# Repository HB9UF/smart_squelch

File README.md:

HB9UF Smart Squelch -- A squelch board with clever logic
========================================================

A typical FM squelch for voice operation quantifies the amount of noise at frequencies above the voice frequency content and opens if said noise energy is sufficiently low. This works because without any input RF signal present, the FM detector produces wideband noise, reaching frequencies of several dozen kHz. A sufficiently strong RF input reduces that noise, the modulation emerges between typically 0 and 3 kHz and similarly, the noise above 3 kHz is reduced. Traditionally, a high-pass filter (HPF) attenuates the modulation while retaining the noise energy, and a subsequent peak-detector quantifies the amount of energy present, and finally a comparator circuit uses the peak detector output voltage to actuate the squelch.

Our squelch circuit is different. First, we use a microcontroller for the squelch logic. This allows us not only to change squelch thresholds without hardware access, but we can also implement more sophisticated squelching logic. For example, we can implement a hard threshold that is used when strong stations key off: The squelch is closed immediately, minimizing the squelch crash that is nothing but the manifestation of discriminator noise during the time-window after key-off and the closing of the squelch. At the same time, we can implement a second threshold for weak stations, e.g. stations far away, with low RF power, fading stations, or mobile stations with picket-fencing. Such stations may overcome the weak, but not the strong threshold. In this case, the squelch remains open for a predetermined time-window (e.g. 1 second) in order not to cut off the weak station. Note that this is superior to simply adding hysteresis to the aforementioned comparator, and that this is mimicking the behaviour of the [MICOR Squelch](http://www.repeater-builder.com/micor/micor-bi-level-squelch-theory.html) system.

The board also contains a number of extra circuitry such as an anti-aliasing low pass filter, a DC/DC converter etc. for integration with our repeater controller. This project is fully open source, the hardware is released under the CC-BY-SA license and the firmware is released under the GPL 2 license. Instructions for compiling and flashing the firmware are documented in a `README` file in the `firmware` subdirectory. The necessary tools and frameworks (ChibiOS and stm32flash) are also included there as git submodules. The circuitry was developed to improve the poor squelch performance of the Yaesu DR-1X repeater and is also successfully used in a number of homebrew 1.3 GHz repeaters.

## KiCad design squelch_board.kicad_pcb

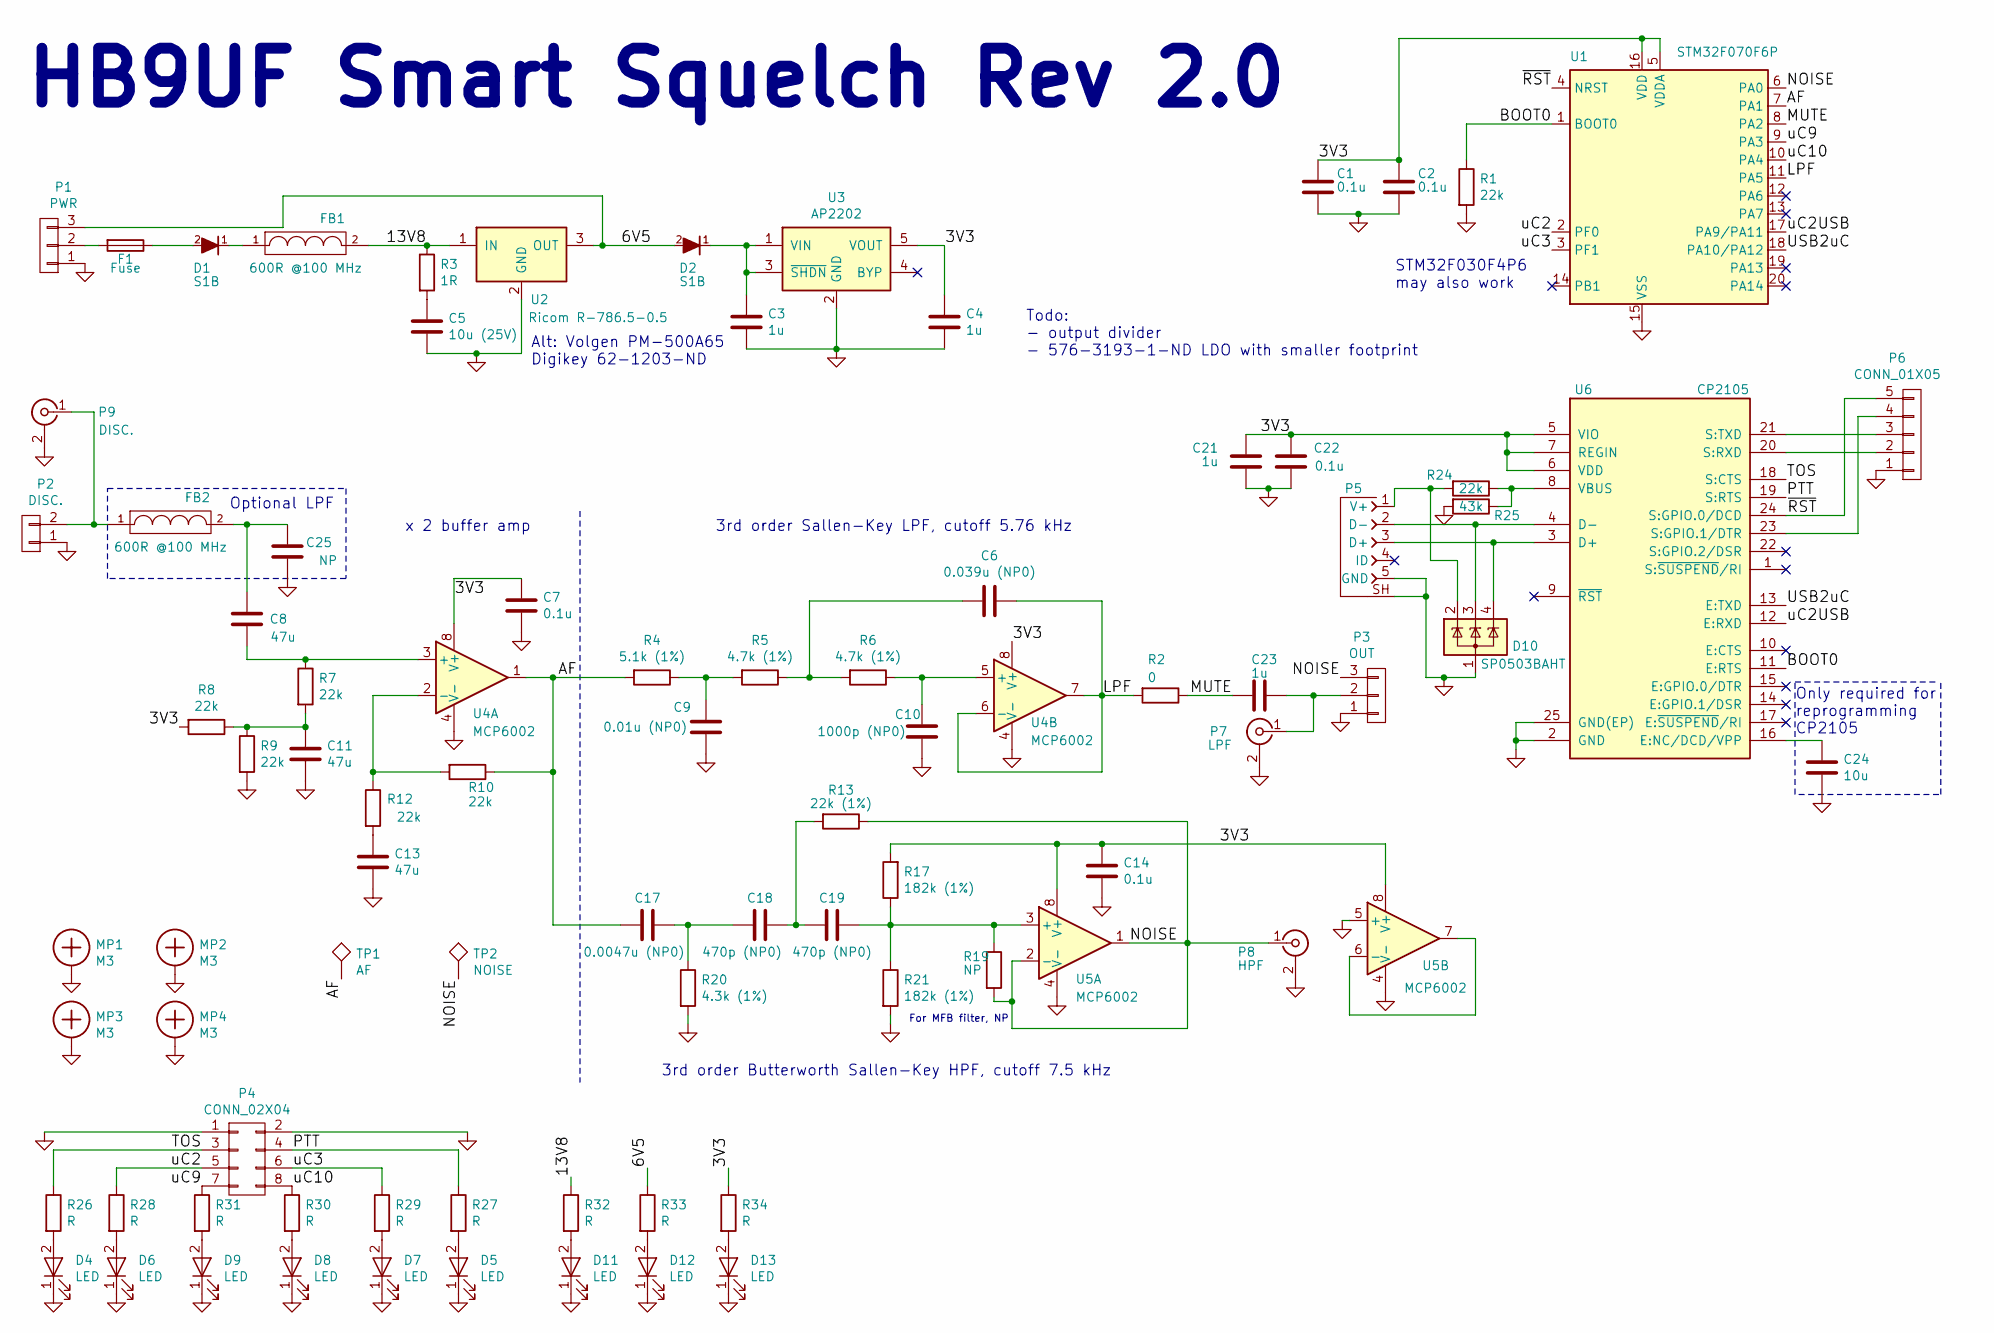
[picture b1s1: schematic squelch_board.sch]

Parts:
C1, C2, C7, C14, C22: 0.1u; C_0603_1608Metric
C3, C4, C21, C23: 1u; C_0603_1608Metric
C5: 10u (25V); C_0805_2012Metric
C6: 0.039u (NP0); C_1206_3216Metric
C8, C11, C13: 47u; C_0805_2012Metric
C9: 0.01u (NP0); C_0603_1608Metric
C10: 1000p (NP0); C_0603_1608Metric
C17: 0.0047u (NP0); C_0603_1608Metric
C18, C19: 470p (NP0); C_0603_1608Metric
C24: 10u; C_0805_2012Metric
C25: NP; C_0603_1608Metric
D1, D2: S1B; D_SMA
D4, D5, D6, D7, D8, D9: LED; LED_0402_1005Metric
D10: SP0503BAHT; SOT-143
D11, D12, D13: LED; LED_0805_2012Metric
F1: Fuse; R_1206_3216Metric
FB1, FB2: 600R @100 MHz; R_0603_1608Metric
MP1, MP2, MP3, MP4: M3; MountingHole_3mm_Pad
P1: PWR; mpt_0,5%2f3-2,54
P2: DISC.; mpt_0,5%2f2-2,54
P3: OUT; mpt_0,5%2f3-2,54
P4: CONN_02X04; PinHeader_2x04_P2.54mm_Horizontal
P5: CONN-10033526-N3212LF; USB_Mini-B_Lumberg_2486_01_Horizontal
P6: CONN_01X05; PinHeader_1x05_P2.54mm_Horizontal
P7: LPF; MOLEX-0734152063
P8: HPF; MOLEX-0734152063
P9: DISC.; MOLEX-0734152063
R1, R7, R8, R9, R10, R12, R24: 22k; R_0603_1608Metric
R2: 0; R_0603_1608Metric
R3: 1R; R_0603_1608Metric
R4: 5.1k (1%); R_0603_1608Metric
R5, R6: 4.7k (1%); R_0603_1608Metric
R13: 22k (1%); R_0603_1608Metric
R17, R21: 182k (1%); R_0603_1608Metric
R19: NP; R_0603_1608Metric
R20: 4.3k (1%); R_0603_1608Metric
R25: 43k; R_0603_1608Metric
R26, R27, R28, R29, R30, R31, R32, R33, R34: R; R_0603_1608Metric
TP1: AF; TESTPOINT-KEYSTONE-5018
TP2: NOISE; TESTPOINT-KEYSTONE-5018
U1: STM32F070F6P; TSSOP-20_4.4x6.5mm_P0.65mm
U2: Ricom R-786.5-0.5; R-78xx-0.5
U3: AP2202; SOT-23-5
U4, U5: MCP6002; MSOP-8_3x3mm_P0.65mm
U6: CP2105; QFN-24-1EP_4x4mm_P0.5mm_EP2.7x2.7mm

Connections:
/3V3: C1.1, C2.1, C4.1, C7.1, C14.1, C21.1, C22.1, R8.2, R17.2, R34.1, U1.5 (VDDA), U1.16 (VDD), U3.5 (VOUT), U4.8 (V+), U5.8 (V+), U6.5 (VIO), U6.6 (VDD), U6.7 (REGIN)
/6V5: D2.2 (A), P1.3, R33.1, U2.3 (OUT)
/13V8: FB1.2, R3.1, R32.1, U2.1 (IN)
/AF: C17.2, R4.2, R10.1, TP1.1, U1.7 (PA1), U4.1
/BOOT0: R1.1, U1.1 (BOOT0), U6.11 (E:RTS)
/LPF: C6.1, R2.2, U1.11 (PA5), U4.6 (-), U4.7
/MUTE: C23.2, R2.1, U1.8 (PA2)
/NOISE: P3.3, P8.1 (In), R13.1, R19.2, TP2.1, U1.6 (PA0), U5.1, U5.2 (-)
/PTT: P4.4, R27.1, U6.19 (S:RTS)
/TOS: P4.3, R26.1, U6.18 (S:CTS)
/USB2uC: U1.18 (PA10/PA12), U6.13 (E:TXD)
/uC2: P4.5, R28.1, U1.2 (PF0)
/uC2USB: U1.17 (PA9/PA11), U6.12 (E:RXD)
/uC3: P4.6, R29.1, U1.3 (PF1)
/uC9: P4.7, R31.1, U1.9 (PA3)
/uC10: P4.8, R30.1, U1.10 (PA4)
/~RST: P6.5, U1.4 (NRST), U6.24 (S:GPIO.0/DCD)
GND: C1.2, C2.2, C3.2, C4.2, C5.2, C7.2, C9.2, C10.2, C11.2, C13.2, C14.2, C21.2, C22.2, C24.2, C25.1, D4.1 (K), D5.1 (K), D6.1 (K), D7.1 (K), D8.1 (K), D9.1 (K), D10.1 (A), D11.1 (K), D12.1 (K), D13.1 (K), MP1.1, MP2.1, MP3.1, MP4.1, P1.1, P2.1, P3.1, P4.1, P4.2, P5.5 (GND), P5.SH (SHIELD), P6.1, P7.2 (Ext), P8.2 (Ext), P9.2 (Ext), R1.2, R9.2, R20.2, R21.2, R25.2, U1.15 (VSS), U2.2 (GND), U3.2 (GND), U4.4 (V-), U5.4 (V-), U5.5 (+), U6.2 (GND), U6.25 (GND(EP))
unnamed: C3.1, D2.1 (K), U3.1 (VIN), U3.3 (~SHDN~)
unnamed: C5.1, R3.2
unnamed: C6.2, R5.1, R6.2
unnamed: C8.1, R7.1, U4.3 (+)
unnamed: C9.1, R4.1, R5.2
unnamed: C10.1, R6.1, U4.5 (+)
unnamed: C11.1, R7.2, R8.1, R9.1
unnamed: C13.1, R12.2
unnamed: C17.1, C18.2, R20.1
unnamed: C18.1, C19.2, R13.2
unnamed: C19.1, R17.1, R19.1, R21.1, U5.3 (+)
unnamed: C23.1, P3.2, P7.1 (In)
unnamed: C24.1, U6.16 (E:NC/DCD/VPP)
unnamed: C8.2, C25.2, FB2.2
unnamed: D1.1 (K), FB1.1
unnamed: D1.2 (A), F1.1
unnamed: D4.2 (A), R26.2
unnamed: D5.2 (A), R27.2
unnamed: D6.2 (A), R28.2
unnamed: D7.2 (A), R29.2
unnamed: D8.2 (A), R30.2
unnamed: D9.2 (A), R31.2
unnamed: D10.2 (K), P5.1 (V+), R24.2
unnamed: D10.3 (K), P5.2 (D-), U6.4 (D-)
unnamed: D10.4 (K), P5.3 (D+), U6.3 (D+)
unnamed: D11.2 (A), R32.2
unnamed: D12.2 (A), R33.2
unnamed: D13.2 (A), R34.2
unnamed: F1.2, P1.2
unnamed: FB2.1, P2.2, P9.1 (In)
unnamed: P6.2, U6.20 (S:RXD)
unnamed: P6.3, U6.21 (S:TXD)
unnamed: P6.4, U6.23 (S:GPIO.1/DTR)
unnamed: R10.2, R12.1, U4.2 (-)
unnamed: R24.1, R25.1, U6.8 (VBUS)
unnamed: U5.6 (-), U5.7

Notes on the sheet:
x 2 buffer amp
3rd order Sallen-Key LPF, cutoff 5.76 kHz
3rd order Butterworth Sallen-Key HPF, cutoff 7.5 kHz
HB9UF Smart Squelch Rev 2.0
For MFB filter, NP
Alt: Volgen PM-500A65 Digikey 62-1203-ND
Only required for reprogramming CP2105
STM32F030F4P6 may also work
Optional LPF
Todo: - output divider - 576-3193-1-ND LDO with smaller footprint

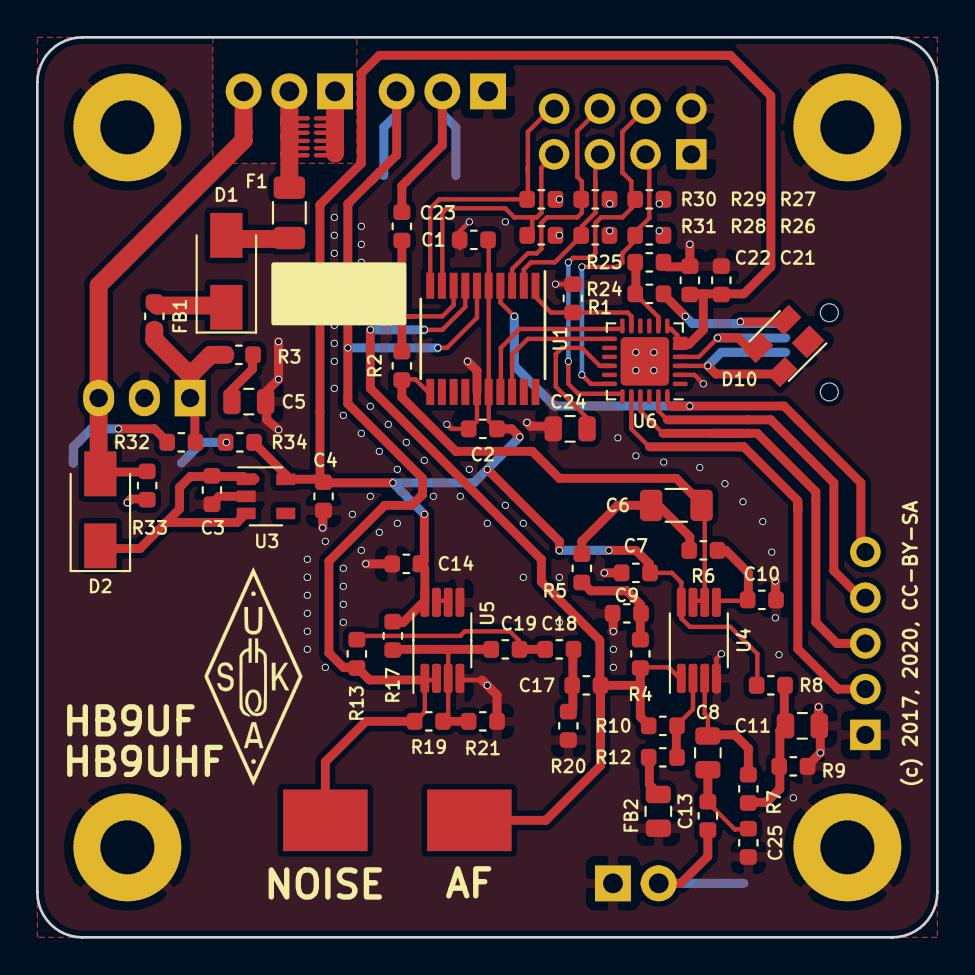
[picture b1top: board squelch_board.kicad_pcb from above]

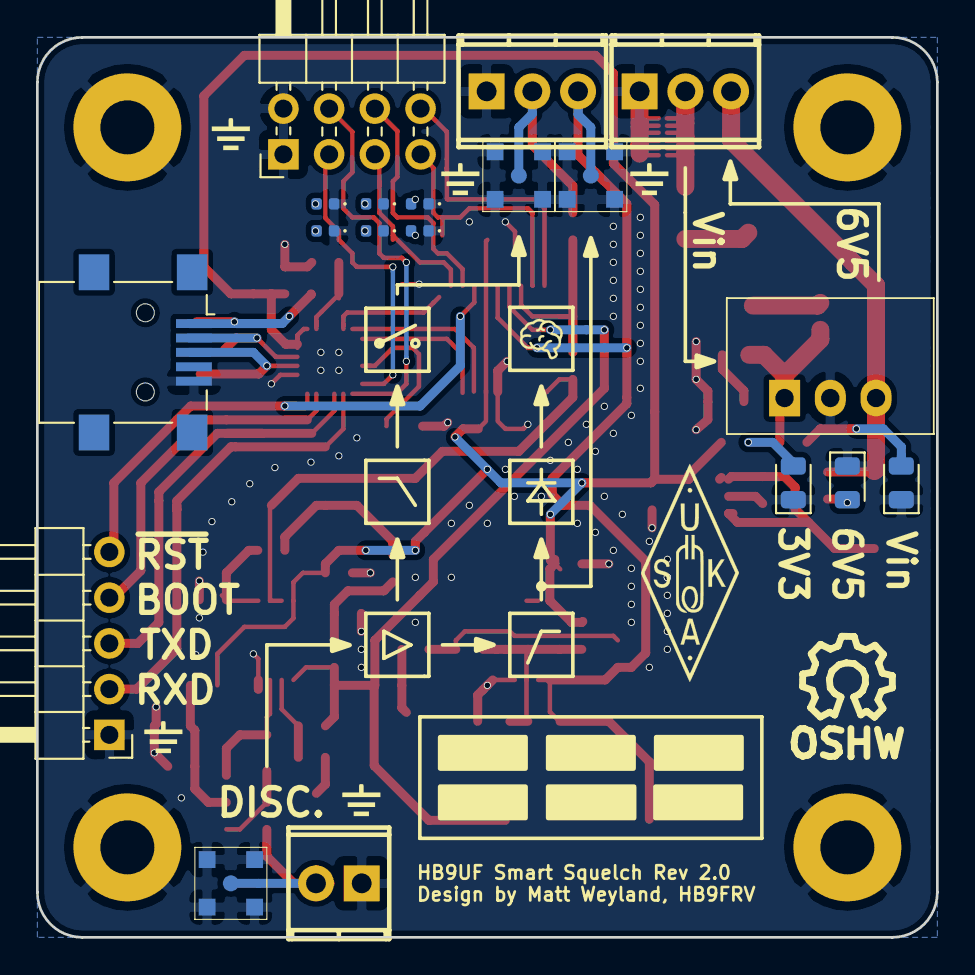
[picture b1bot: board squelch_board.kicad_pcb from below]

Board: 2 copper layers, 50.0 x 50.0 mm, 90 parts (25 on the bottom side), 54 nets.

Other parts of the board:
SYM: Symbol_OSHW-Logo_SilkScreen_07Jul2012; Symbol_OSHW-Logo_SilkScreen
VAL: GND
VAL#2, VAL#3, VAL#4, VAL#5: GND

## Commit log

2020-06-07 Adding .gitignore file for KiCad
2020-06-07 Initial commit of board files
2020-06-07 Upgrading schematic to current version of KiCad
2020-06-07 Adding git submodule for ChibiOS 3.0.3 on which firmware is based
2020-06-07 Adding V 1.3 firmware
2020-06-07 Adding documentation and helper scripts to program the microcontroller.
2020-06-07 Modifying .gitignore to ignore firmware binaries.
2020-06-07 Adding missing KiCad files.
2020-06-07 Adding KiCad backup directory to .gitignore file
2020-06-07 Adding linker file for STM32F070
2020-06-07 Alter Makefile to compile for STM32F070 target (was: STM32F030)
2020-06-07 Re-implementing main.c from scratch
2020-06-07 Actuating squelch pin GPIOF1.
2020-06-07 Moving io functions to separate io module (io.c, io.h)
2020-06-07 Removing unnecessary #include "string.h"
2020-06-07 Moving circular buffer code to backlog.{c,h} module.
2020-06-07 Make programming somewhat faster by reducing sleep time.
2020-06-07 Moving ADC-related code to dedicated adc module (adc.{c,h})
2020-06-07 Moving UART-related code to uart module (uart.{c,h})
2020-06-07 Reducing sampling time (since we can, the S&H circuit is driven by OPA)
2020-06-07 Adding code documentation
2020-06-07 Disabling GPIOA4 idle-tracker
2020-06-07 Bugfix: Don't hardcode size of backlog buffer.
2020-06-07 Adding arming step (and comments controller logic)
2020-06-08 Starting with rev 2.0 mods: Removing detector circuitry
2020-06-08 Removing R23 (selector for OPA rail voltage and potential ripple rejection)
2020-06-08 Adding fencing vias around AF_BUF track
2020-06-08 Slight modification to avoid overlapping country-yard errors.
2020-06-08 Re-aligning silk labels to prevent them from overlapping.
2020-06-08 Renaming "HPF" to "NOISE" in schematic and on silk screen.
2020-06-08 Swapping out STM32F030F4P6 for STM32F070F6P
2020-06-08 Slight rearrangement of schematic, renaming nodes for consistency.
2020-06-08 Bumping version number to 2.0
2020-06-08 Swapping out footprints for current ones in order to have 3d models
2020-06-08 Adding HB9UF artwork on backside of PCB
2020-06-08 Moving testpoints to board edge
2020-06-08 Slight reduction of white silk square for fuse rating
2020-06-08 Configuring 3d model for testpoint
2020-06-08 Hiding USB connector reference designator
2020-06-09 Changing silk screen block diagram: brin pictogram
    Brain pictogrm is licensed under a CC-BY license, jessie_vp is
    attributed for the original work. Source:
    https://thenounproject.com/term/brain/35201/
2020-06-09 Improving programming instructions.
2020-06-09 Adding note to schematic about optional input LPF
2020-06-09 Renaming "Squelch Board" to "HB9UF Smart Squelch"
2020-06-09 Adding README file, schematics and 3d rendering of project.
2020-06-09 Adding PDF version of schematic.
2020-06-10 Minor corrections in README files
2020-06-10 Fixing direction of power supply arrows on silk screen
2020-06-10 Minor rearrangement of resistor designator
2020-06-10 Improving wording of README file

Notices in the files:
squelch_board.kicad_pcb:
(c) 2017, 2020, CC-BY-SA
